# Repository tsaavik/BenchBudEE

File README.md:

BenchBudEE
==========

The Session 1 Project For Contextual Electronics  
More info here: http://contextualelectronics.com/the-benchbudee/

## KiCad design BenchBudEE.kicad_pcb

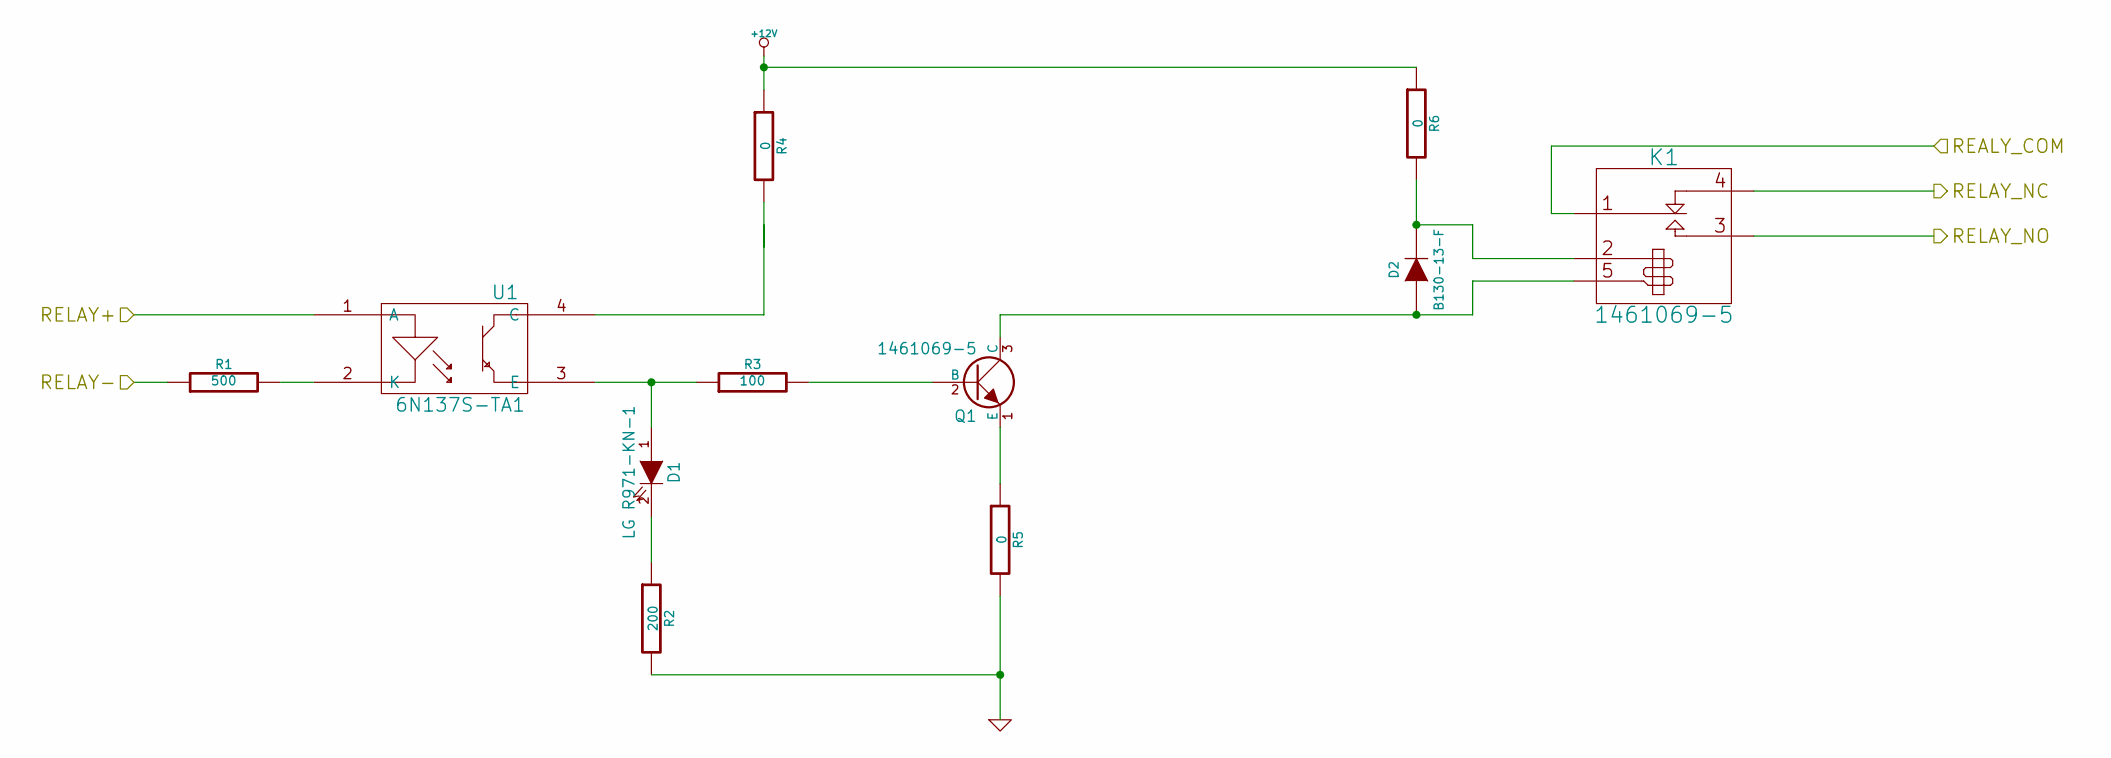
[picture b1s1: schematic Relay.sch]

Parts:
D1: LG R971-KN-1
D2: B130-13-F; MFG Part Number B130-13-F
K1: 1461069-5
Q1: 1461069-5; MFG Part Number 1461069-5
R1: 500
R2: 200
R3: 100
R4, R5, R6: 0
U1: 6N137S-TA1; MFG Part Number 6N137S-TA1

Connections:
+12V: R4.1, R6.1; also elsewhere on the board
/Relay/REALY_COM: K1.1 (C1); also elsewhere on the board
/Relay/RELAY+: U1.1 (A); also elsewhere on the board
/Relay/RELAY-: R1.1; also elsewhere on the board
/Relay/RELAY_NC: K1.4 (NC); also elsewhere on the board
/Relay/RELAY_NO: K1.3 (NO); also elsewhere on the board
GND: R2.2, R5.2; also elsewhere on the board
unnamed: R1.2, U1.2 (K)
unnamed: D2.2 (K), K1.2 (Coil+), R6.2
unnamed: D2.1 (A), K1.5 (Coil-), Q1.3 (C)
unnamed: D1.2 (K), R2.1
unnamed: R4.2, U1.4 (C)
unnamed: Q1.1 (E), R5.1
unnamed: Q1.2 (B), R3.2
unnamed: D1.1 (A), R3.1, U1.3 (E)

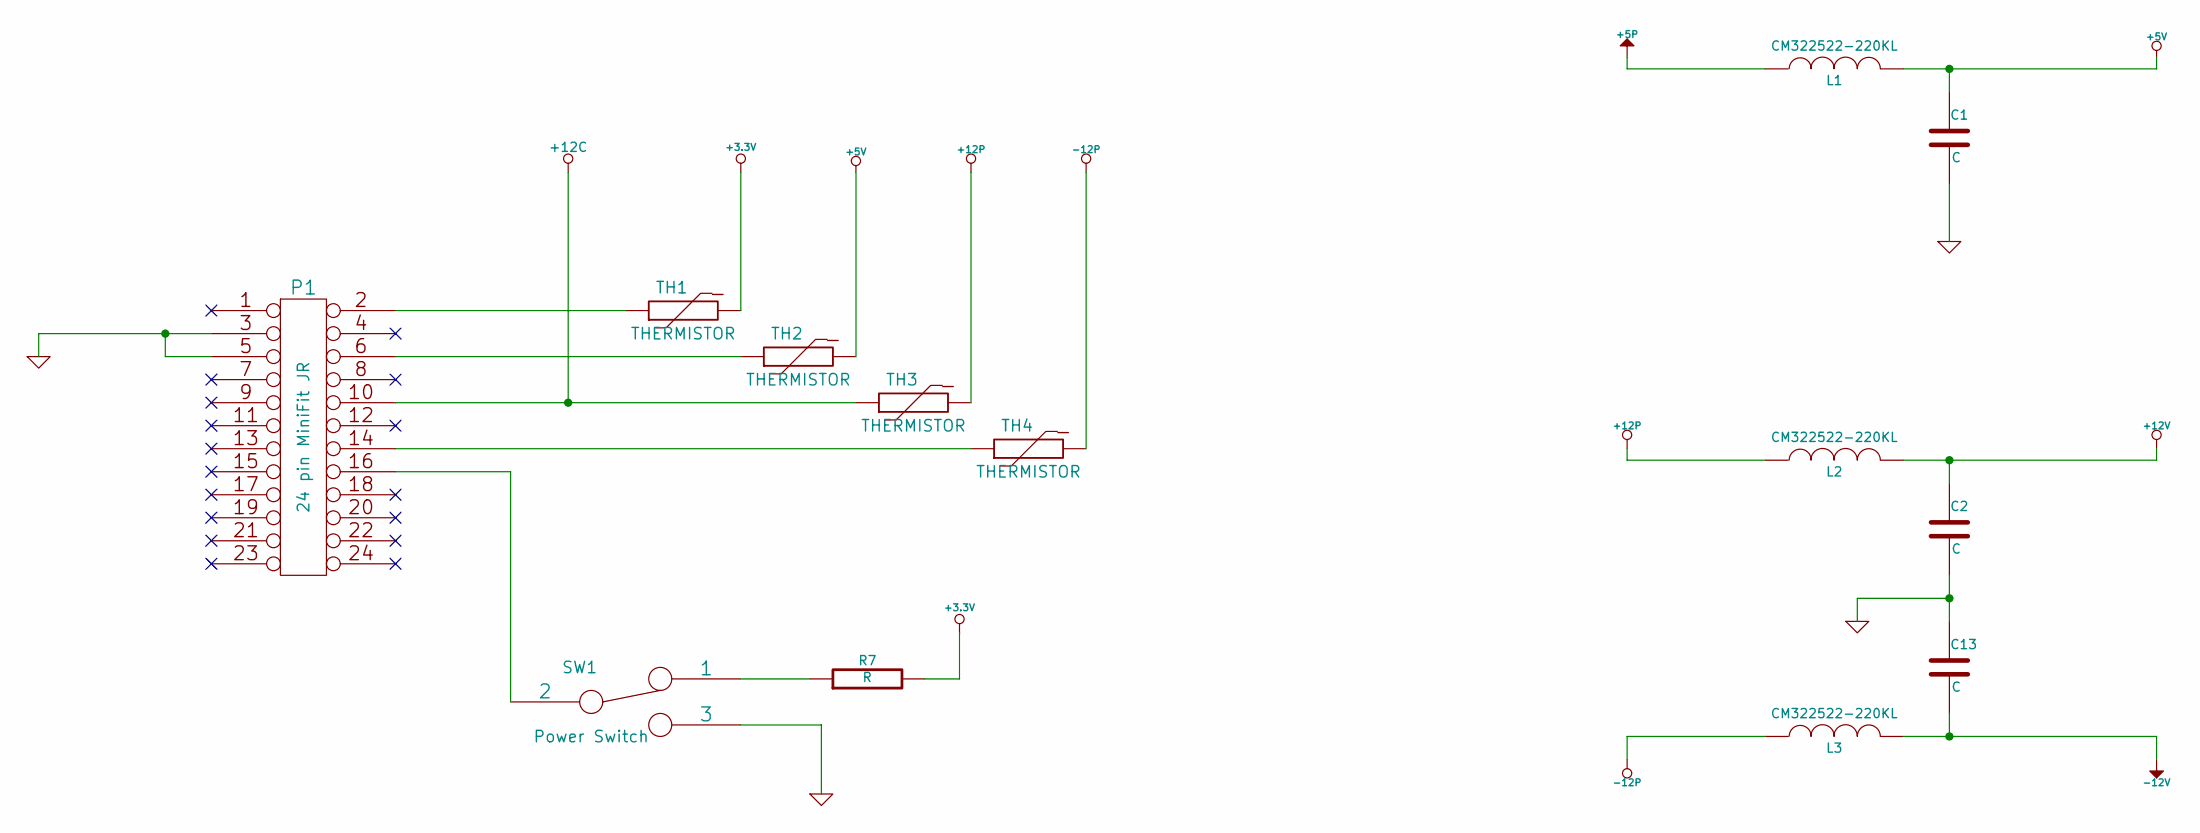
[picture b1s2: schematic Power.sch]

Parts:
C1, C2, C13: C
L1, L2, L3: CM322522-220KL; MFG Part Number CM322522-220KL
P1: 24 pin MiniFit JR; MFG Part Number 39-30-1240
R7: R
SW1: Power Switch; MFG Part Number OS102011MA1QN1
TH1, TH2, TH3, TH4: THERMISTOR; MFG Part Number MINISMDC050F-2

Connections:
+3.3V: R7.2, TH1.2; also elsewhere on the board
+5V: C1.1, L1.2, TH2.2; also elsewhere on the board
+12C: P1.10, TH3.1
+12P: L2.1, TH3.2; also elsewhere on the board
+12V: C2.1, L2.2; also elsewhere on the board
-12P: L3.1, TH4.2
-12V: C13.2, L3.2; also elsewhere on the board
GND: C1.2, C2.2, C13.1, P1.3, P1.5, SW1.3; also elsewhere on the board
unnamed: P1.14, TH4.1
unnamed: P1.6, TH2.1
unnamed: P1.2, TH1.1
unnamed: P1.16, SW1.2
unnamed: R7.1, SW1.1

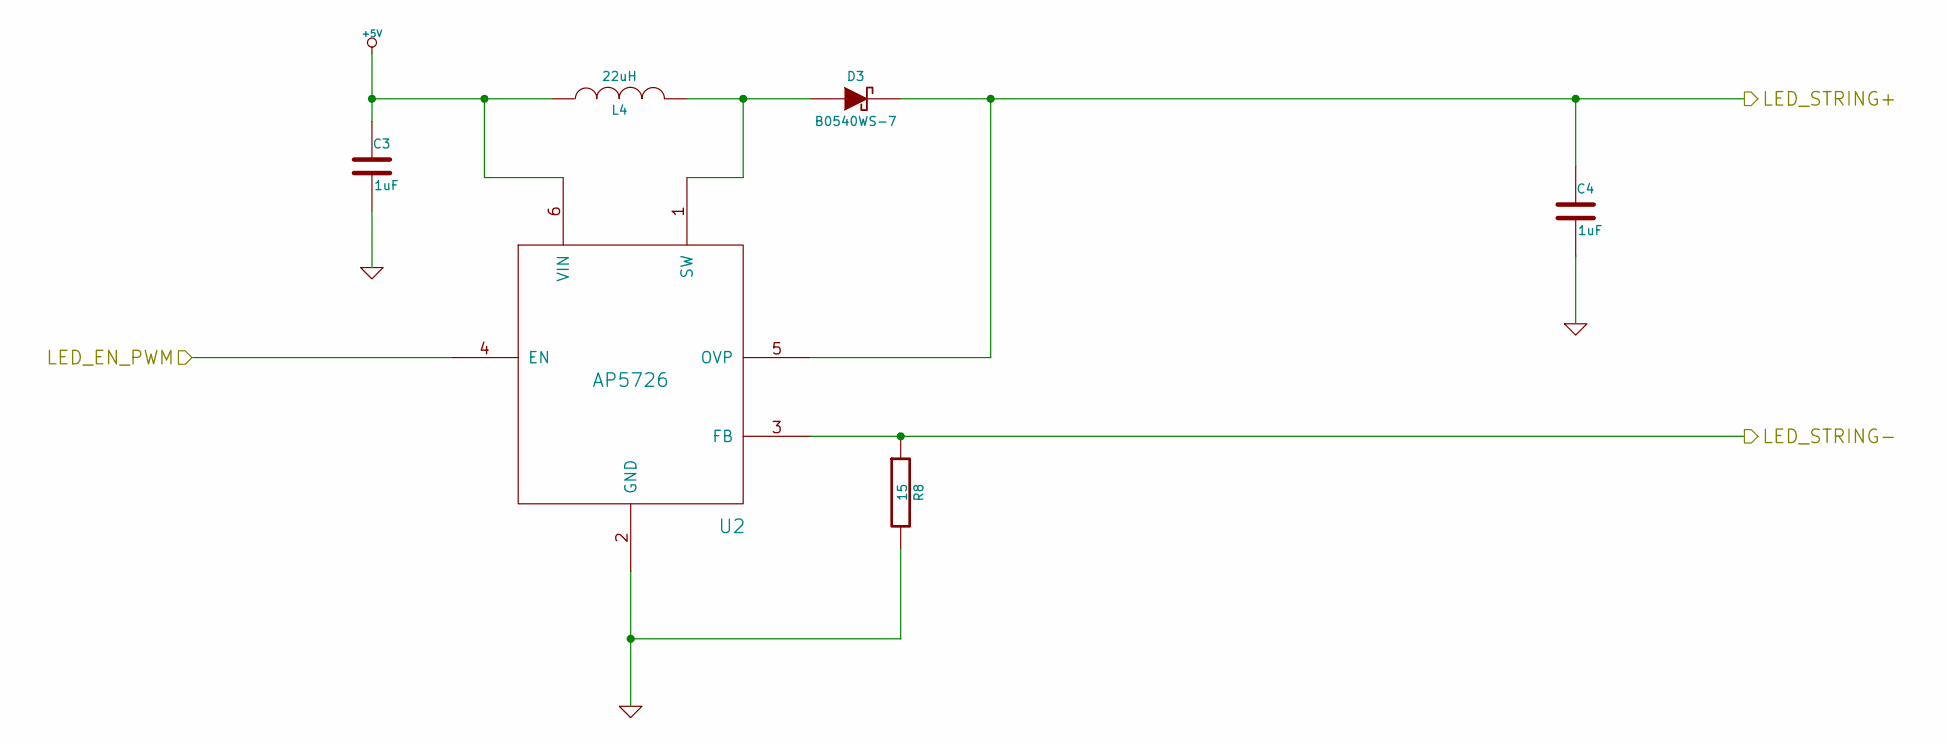
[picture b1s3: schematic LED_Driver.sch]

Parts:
C3, C4: 1uF
D3: B0540WS-7; MFG Part Number B0540WS-7
L4: 22uH; MFG Part Number NR4012T220M
R8: 15
U2: AP5726

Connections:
+5V: C3.1, L4.1, U2.6 (VIN); also elsewhere on the board
/Arduino/LED_EN_PWM: U2.4 (EN); also elsewhere on the board
/LED_Driver/LED_STRING+: C4.1, D3.2 (K), U2.5 (OVP); also elsewhere on the board
/LED_Driver/LED_STRING-: R8.1, U2.3 (FB); also elsewhere on the board
GND: C3.2, C4.2, R8.2, U2.2 (GND); also elsewhere on the board
unnamed: D3.1 (A), L4.2, U2.1 (SW)

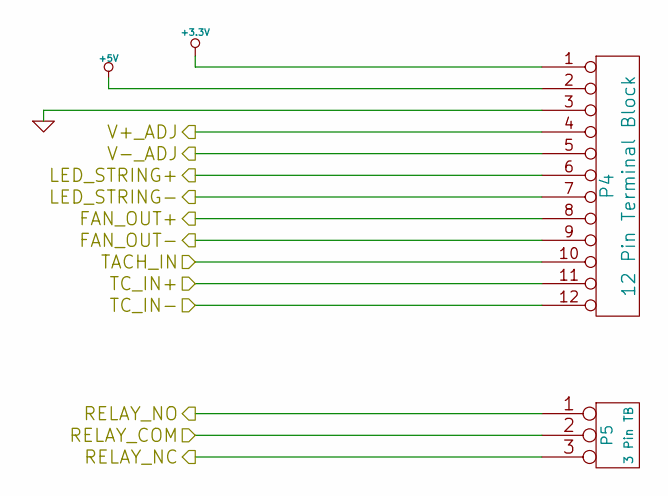
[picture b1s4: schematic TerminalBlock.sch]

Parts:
P4: 12 Pin Terminal Block; MFG Part Number 1706251
P5: 3 Pin TB; MFG Part Number 1990986

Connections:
+3.3V: P4.1; also elsewhere on the board
+5V: P4.2; also elsewhere on the board
/Fan/FAN_OUT+: P4.8; also elsewhere on the board
/Fan/FAN_OUT-: P4.9; also elsewhere on the board
/Fan/TACH_IN: P4.10; also elsewhere on the board
/LED_Driver/LED_STRING+: P4.6; also elsewhere on the board
/LED_Driver/LED_STRING-: P4.7; also elsewhere on the board
/PowerAdjustmentMonitor/V+_ADJ: P4.4; also elsewhere on the board
/PowerAdjustmentMonitor/V-_ADJ: P4.5; also elsewhere on the board
/Relay/REALY_COM: P5.2 (PM); also elsewhere on the board
/Relay/RELAY_NC: P5.3; also elsewhere on the board
/Relay/RELAY_NO: P5.1; also elsewhere on the board
/Thermocouple/TC IN +: P4.11; also elsewhere on the board
/Thermocouple/TC IN -: P4.12; also elsewhere on the board
GND: P4.3; also elsewhere on the board

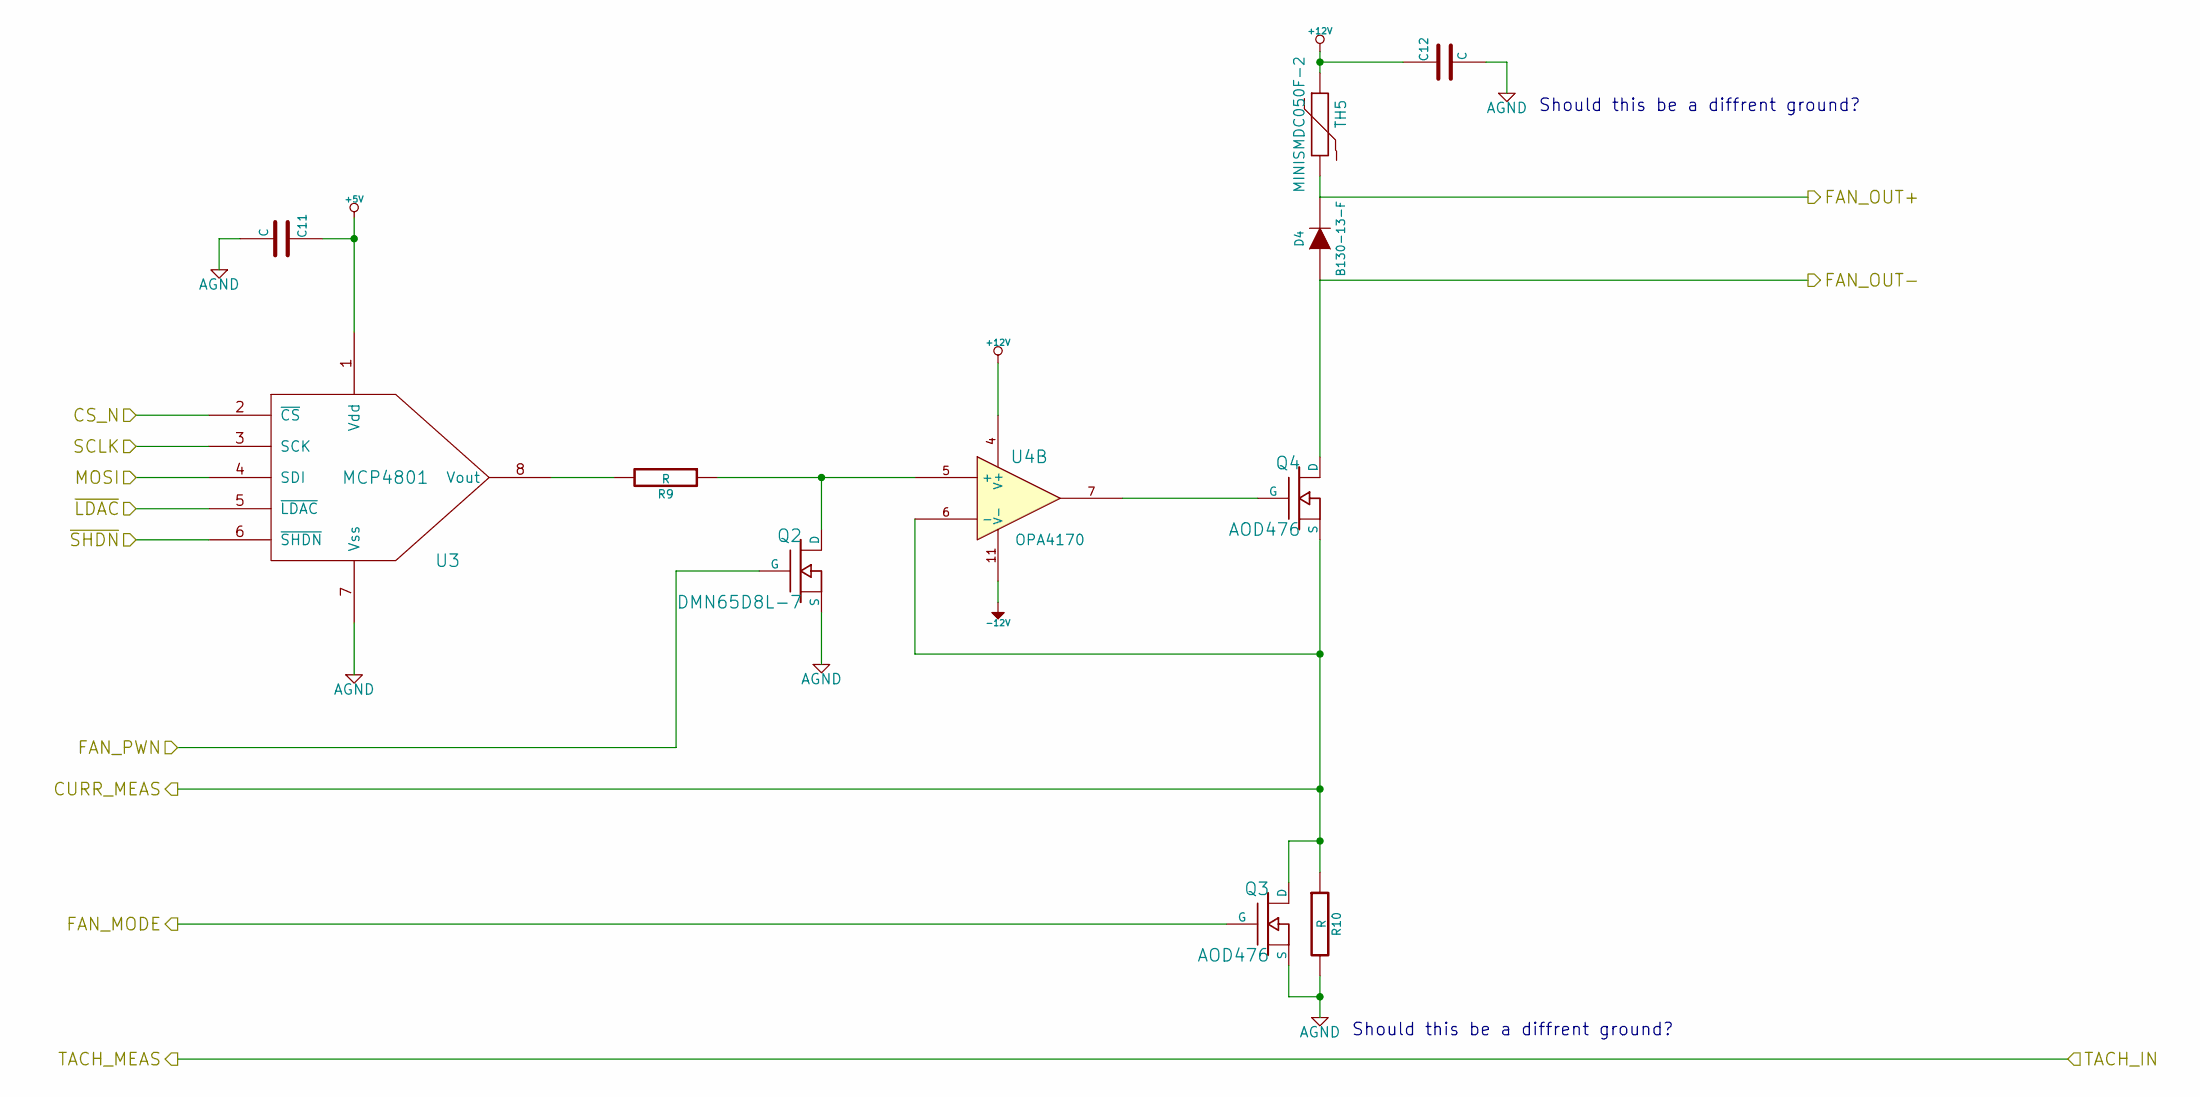
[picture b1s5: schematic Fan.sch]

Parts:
C11, C12: C
D4: B130-13-F; MFG Part Number B130-13-F
Q2: DMN65D8L-7; MFG Part Number DMN65D8L-7
Q3, Q4: AOD476; MFG Part Number AOD476
R9, R10: R
TH5: MINISMDC050F-2; MFG Part Number MINISMDC050F-2
U3: MCP4801
U4: OPA4170

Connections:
+5V: C11.1, U3.1 (Vdd); also elsewhere on the board
+12V: C12.1, TH5.1, U4.4 (V+); also elsewhere on the board
-12V: U4.11 (V-); also elsewhere on the board
/Arduino/CURR_MEAS: Q3.2 (D), Q4.3 (S), R10.1, U4.6 (-); also elsewhere on the board
/Arduino/FAN_MODE: Q3.1 (G); also elsewhere on the board
/Arduino/FAN_PWM: Q2.G; also elsewhere on the board
/Arduino/MOSI: U3.4 (SDI); also elsewhere on the board
/Arduino/SCLK: U3.3 (SCK); also elsewhere on the board
/Arduino/~LDAC: U3.5 (~LDAC); also elsewhere on the board
/Arduino/~SHDN: U3.6 (~SHDN); also elsewhere on the board
/Fan/CS_N: U3.2 (~CS); also elsewhere on the board
/Fan/FAN_OUT+: D4.2 (K), TH5.2; also elsewhere on the board
/Fan/FAN_OUT-: D4.1 (A), Q4.2 (D); also elsewhere on the board
AGND: C11.2, C12.2, Q2.S, Q3.3 (S), R10.2, U3.7 (Vss); also elsewhere on the board
unnamed: Q4.1 (G), U4.7
unnamed: Q2.D, R9.1, U4.5 (+)
unnamed: R9.2, U3.8 (Vout)

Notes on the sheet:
Should this be a diffrent ground?

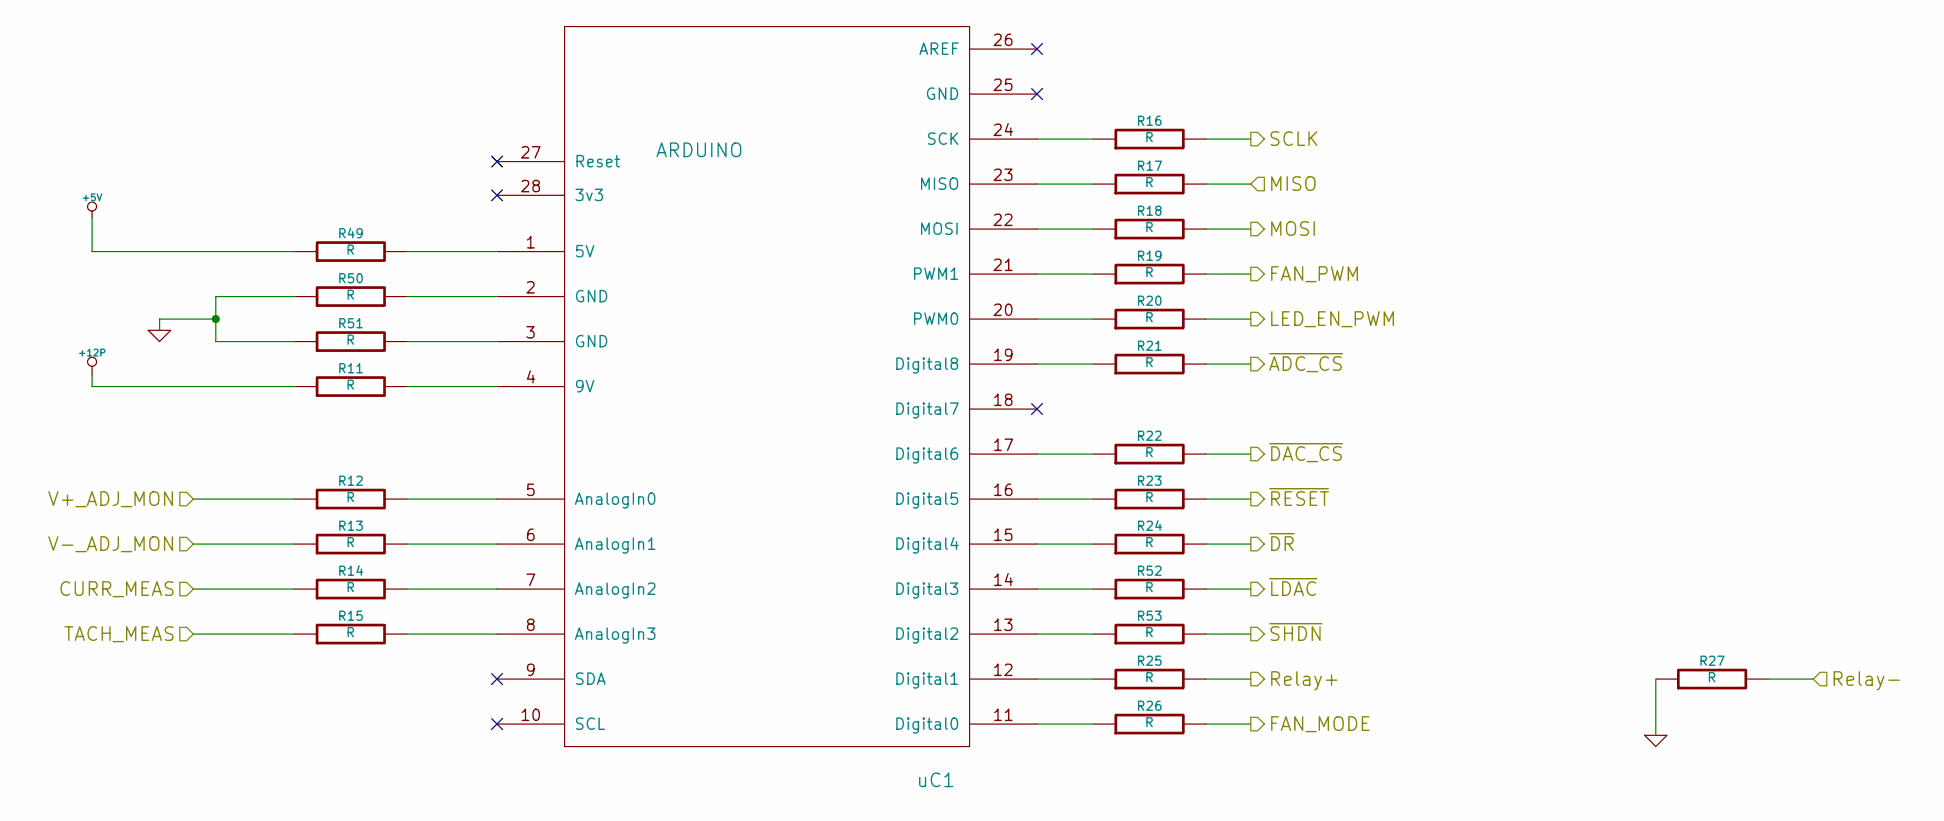
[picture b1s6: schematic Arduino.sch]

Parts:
R11, R12, R13, R14, R15, R16, R17, R18, R19, R20, R21, R22, R23, R24, R25, R26, R27, R49, R50, R51, R52, R53: R
uC1: ARDUINO

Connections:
+5V: R49.1; also elsewhere on the board
+12P: R11.1; also elsewhere on the board
/Arduino/CURR_MEAS: R14.1; also elsewhere on the board
/Arduino/FAN_MODE: R26.2; also elsewhere on the board
/Arduino/FAN_PWM: R19.2; also elsewhere on the board
/Arduino/LED_EN_PWM: R20.2; also elsewhere on the board
/Arduino/MISO: R17.2; also elsewhere on the board
/Arduino/MOSI: R18.2; also elsewhere on the board
/Arduino/SCLK: R16.2; also elsewhere on the board
/Arduino/V+_ADJ_MON: R12.1; also elsewhere on the board
/Arduino/V-_ADJ_MON: R13.1; also elsewhere on the board
/Arduino/~ADC_CS: R21.2; also elsewhere on the board
/Arduino/~DR: R24.2; also elsewhere on the board
/Arduino/~LDAC: R52.2; also elsewhere on the board
/Arduino/~RESET: R23.2; also elsewhere on the board
/Arduino/~SHDN: R53.2; also elsewhere on the board
/Fan/CS_N: R22.2; also elsewhere on the board
/Fan/TACH_IN: R15.1; also elsewhere on the board
/Relay/RELAY+: R25.2; also elsewhere on the board
/Relay/RELAY-: R27.2; also elsewhere on the board
GND: R27.1, R50.1, R51.1; also elsewhere on the board
unnamed: R25.1, uC1.12 (Digital1)
unnamed: R19.1, uC1.21 (PWM1)
unnamed: R21.1, uC1.19 (Digital8)
unnamed: R18.1, uC1.22 (MOSI)
unnamed: R16.1, uC1.24 (SCK)
unnamed: R11.2, uC1.4 (9V)
unnamed: R26.1, uC1.11 (Digital0)
unnamed: R22.1, uC1.17 (Digital6)
unnamed: R20.1, uC1.20 (PWM0)
unnamed: R15.2, uC1.8 (AnalogIn3)
unnamed: R14.2, uC1.7 (AnalogIn2)
unnamed: R13.2, uC1.6 (AnalogIn1)
unnamed: R12.2, uC1.5 (AnalogIn0)
unnamed: R17.1, uC1.23 (MISO)
unnamed: R49.2, uC1.1 (5V)
unnamed: R51.2, uC1.3 (GND)
unnamed: R50.2, uC1.2 (GND)
unnamed: R23.1, uC1.16 (Digital5)
unnamed: R53.1, uC1.13 (Digital2)
unnamed: R52.1, uC1.14 (Digital3)
unnamed: R24.1, uC1.15 (Digital4)

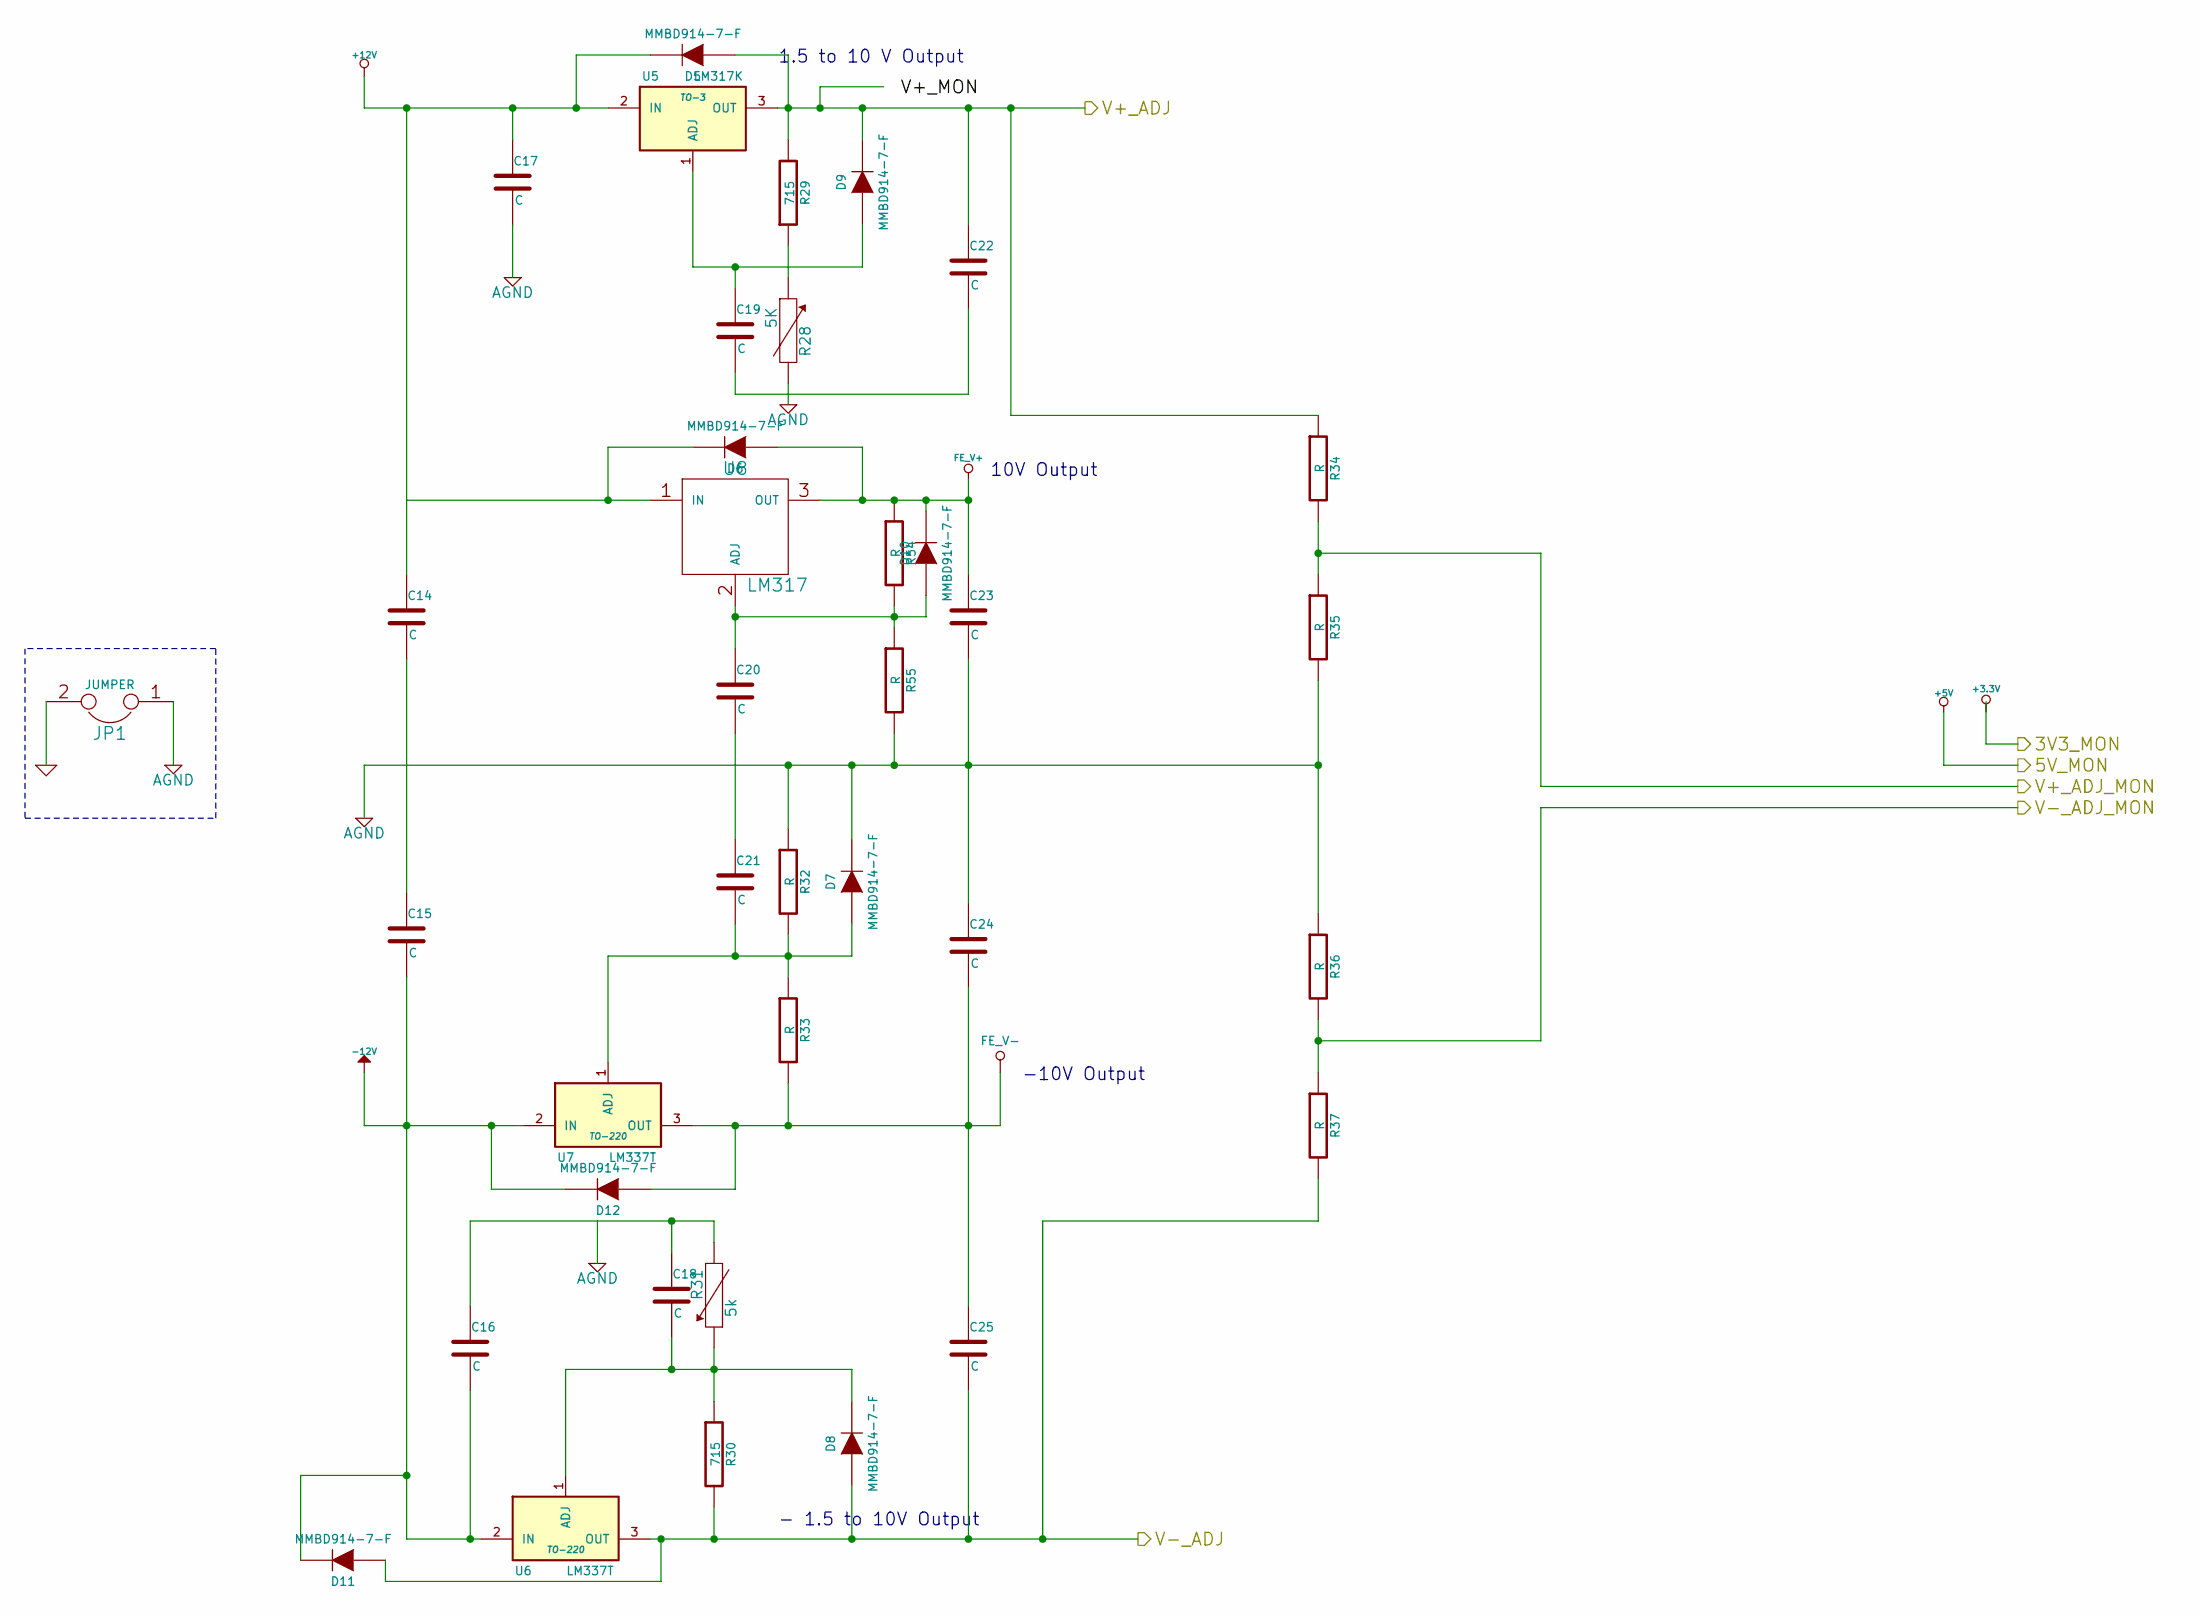
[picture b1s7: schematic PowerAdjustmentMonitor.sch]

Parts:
C14, C15, C16, C17, C18, C19, C20, C21, C22, C23, C24, C25: C
D5, D6, D7, D8, D9, D10, D11, D12: MMBD914-7-F
JP1: JUMPER
R28: 5K
R29: 715
R30: 715
R31: 5k
R32, R33, R54, R55: R
R34, R35, R36, R37: R
U5: LM317K; TO-3
U6, U7: LM337T; TO-220
U8: LM317

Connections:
+12V: C14.1, C17.1, D5.2 (K), U5.2 (IN); also elsewhere on the board
-12V: C15.2, C16.2, D11.2 (K), D12.2 (K), U6.2 (IN), U7.2 (IN); also elsewhere on the board
/Arduino/V+_ADJ_MON: R34.2, R35.1; also elsewhere on the board
/Arduino/V-_ADJ_MON: R36.2, R37.1; also elsewhere on the board
/PowerAdjustmentMonitor/V+_ADJ: C22.1, D5.1 (A), D9.2 (K), R29.2, R34.1, U5.3 (OUT); also elsewhere on the board
/PowerAdjustmentMonitor/V-_ADJ: C25.2, D8.1 (A), D11.1 (A), R30.2, R37.2, U6.3 (OUT); also elsewhere on the board
AGND: C17.2, C23.2, C24.1, D7.2 (K), JP1.1, R28.2, R32.1, R35.2, R36.1, R55.2; also elsewhere on the board
FE_V+: C23.1, D6.1 (A), D10.2 (K), R54.1, U8.3 (OUT)
FE_V-: C24.2, C25.1, D12.1 (A), R33.2, U7.3 (OUT)
GND: JP1.2; also elsewhere on the board
unnamed: C20.2, C21.1
unnamed: C16.1, C18.1, R31.2
unnamed: C19.2, C22.2
unnamed: C14.2, C15.1
unnamed: R28.1, R29.1
unnamed: C19.1, D9.1 (A), U5.1 (ADJ)
unnamed: D6.2 (K), U8.1 (IN)
unnamed: C20.1, D10.1 (A), R54.2, R55.1, U8.2 (ADJ)
unnamed: C21.2, D7.1 (A), R32.2, R33.1, U7.1 (ADJ)
unnamed: C18.2, D8.2 (K), R30.1, R31.1, U6.1 (ADJ)

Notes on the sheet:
1.5 to 10 V Output
10V Output
-10V Output
- 1.5 to 10V Output

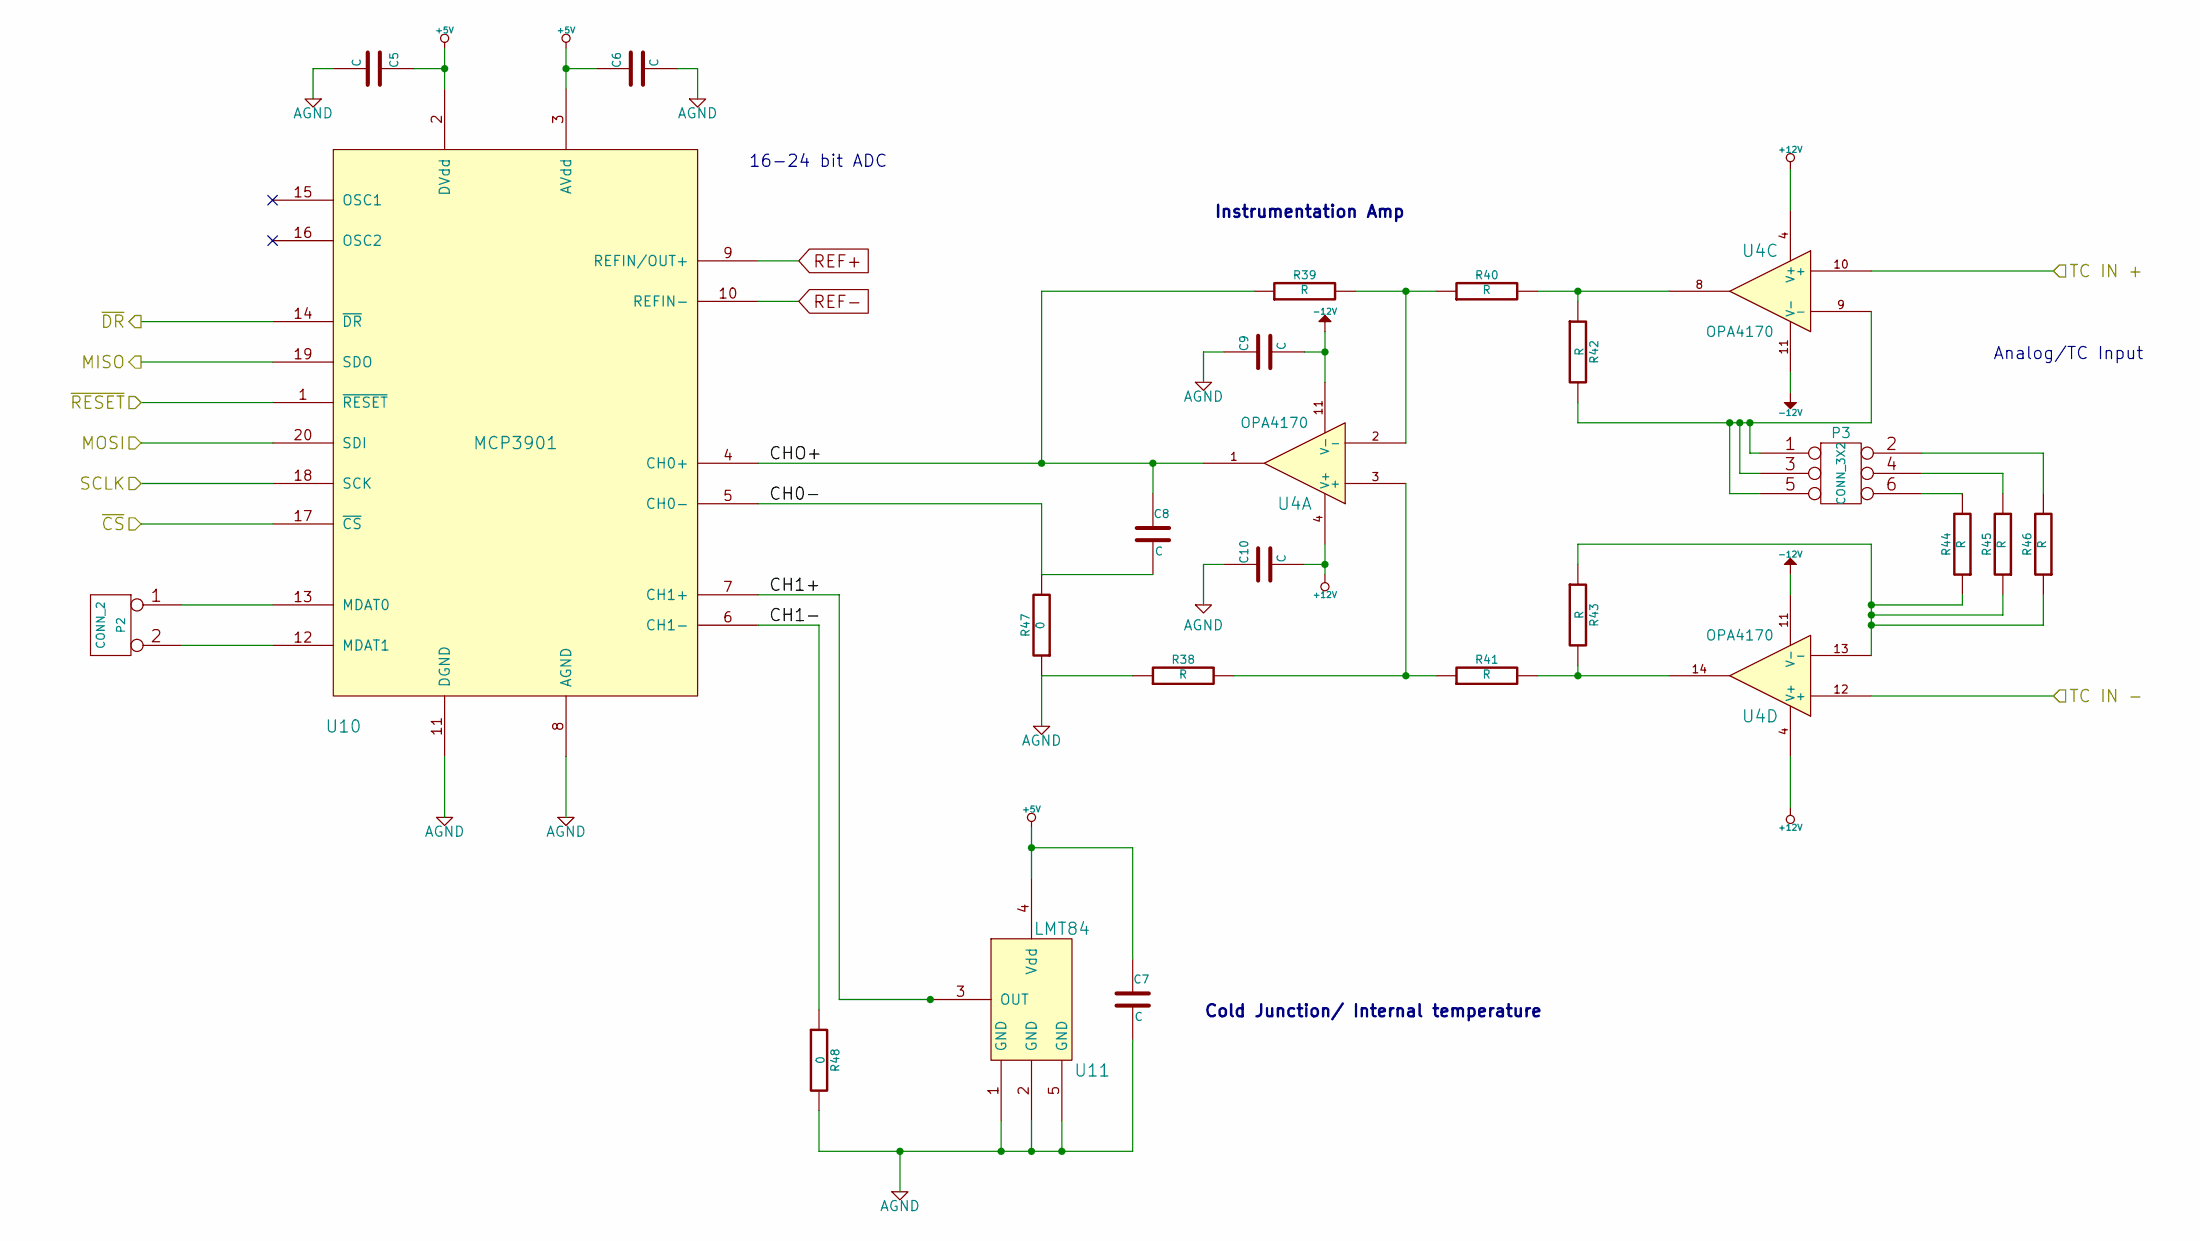
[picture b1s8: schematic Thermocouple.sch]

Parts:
C5, C6, C7, C8, C9, C10: C
P2: CONN_2
P3: CONN_3X2
R38, R39, R40, R41, R42, R43, R44, R45, R46: R
R47, R48: 0
U4: OPA4170
U10: MCP3901
U11: LMT84

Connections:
+5V: C5.1, C6.1, C7.1, U10.2 (DVdd), U10.3 (AVdd), U11.4 (Vdd); also elsewhere on the board
+12V: C10.2, U4.4 (V+); also elsewhere on the board
-12V: C9.2, U4.11 (V-); also elsewhere on the board
/Arduino/MISO: U10.19 (SDO); also elsewhere on the board
/Arduino/MOSI: U10.20 (SDI); also elsewhere on the board
/Arduino/SCLK: U10.18 (SCK); also elsewhere on the board
/Arduino/~ADC_CS: U10.17 (~CS); also elsewhere on the board
/Arduino/~DR: U10.14 (~DR); also elsewhere on the board
/Arduino/~RESET: U10.1 (~RESET); also elsewhere on the board
/Thermocouple/CH0-: C8.2, R47.2, U10.5 (CH0-)
/Thermocouple/CH1+: U10.7 (CH1+), U11.3 (OUT)
/Thermocouple/CH1-: R48.1, U10.6 (CH1-)
/Thermocouple/CHO+: C8.1, R39.1, U4.1, U10.4 (CH0+)
/Thermocouple/TC IN +: U4.10 (+); also elsewhere on the board
/Thermocouple/TC IN -: U4.12 (+); also elsewhere on the board
AGND: C5.2, C6.2, C7.2, C9.1, C10.1, R38.1, R47.1, R48.2, U10.8 (AGND), U10.11 (DGND), U11.1 (GND), U11.2 (GND), U11.5 (GND); also elsewhere on the board
unnamed: P2.1, U10.13 (MDAT0)
unnamed: P2.2 (PM), U10.12 (MDAT1)
unnamed: P3.2, R46.2
unnamed: P3.4, R45.2
unnamed: P3.6, R44.2
unnamed: R41.2, R43.2, U4.14
unnamed: R40.2, R42.1, U4.8
unnamed: R39.2, R40.1, U4.2 (-)
unnamed: R38.2, R41.1, U4.3 (+)
unnamed: R43.1, R44.1, R45.1, R46.1, U4.13 (-)
unnamed: P3.1, P3.3, P3.5, R42.2, U4.9 (-)

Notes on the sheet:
Instrumentation Amp
Cold Junction/ Internal temperature
16-24 bit ADC
Analog/TC Input

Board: 4 copper layers, 126 parts (64 on the bottom side), 103 nets, no tracks yet.

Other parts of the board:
V2006B Heatsink, V2006B Heatsink#2: VAL**; V2006B_Heatsink

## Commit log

2014-01-30 Module 2.11: create blank schematic/layout
2014-01-31 Module 2: creating a schematic skeleton Added sub-schematics for fan/led/relay/power/etc
2014-01-31 Module 2, Unit 13 Defining Your Inputs and Outputs
2014-02-05 3.3 Thermocouple Module - Initial Design
2014-02-05 3.4 Understanding The Current/Fan Driver Module Added circuit to the Current/Fan Driver module
2014-02-07 3.5 Understanding The Relay Module
2014-02-07 3.6 Understanding The Power Protection And Filtering Module Added the power monitor/filtering sub-schematic
2014-02-07 Put the power schematic in the wrong sub-module (PowerAdjustmentMonitor)
2014-02-07 Not sure what I changed
2014-02-07 files got touched because I did a commit -a and dropbox synced it
2014-02-07 3.7 Understanding The Power Control, Conditioning And Monitoring Module Prior to addition of adjustable resistor. Acidently did save-whole-project
2014-02-07 Added variable resistor(s) to LM317's output
2014-02-07 Forgot the V+_ADJ pin, fixed
2014-02-07 fixed pin name typo 5V5_MON => 5V_MON
2014-02-07 Added hierarchical pins to PowerAdjustmentMonitor
2014-02-08 Added AP5726 led dimmer chip to local library
2014-02-08 3.8 Understanding The LED Driver Module
2014-02-10 3.9 Added Arduino
2014-02-10 3.9 Understanding The Arduino Module Added content to Arduino and block (header) modules
2014-02-10 3.10 Revisiting The Current/Fan Module End of Module 3, lots of cleanup/changes all over the place.
2014-02-13 Fixed a mistake on the arduino Digital pins
2014-02-13 replaced faulty arduino part with updated library
2014-02-16 added *bak to prevent checkin of board backups
2014-02-16 4.18 Initial board layout and design rules mods
2014-02-16 Keyboard shortcuts for BenchBudEE (changed layer selection keys 1-9)
2014-02-16 4.18 Video 2 Changed design rules for pin spacing
2014-02-18 Update README.md
    added image
2014-02-19 5.3 Video 1/2 Associating and Placing the Relay Module
2014-02-20 Added te-spdt relay, sma and smd-8 footprints
2014-02-20 5.3 Video 2/2 Associating and Placing the Relay Module
2014-02-21 5.4 Video 1/2 Associating and Placing the Thermocouple Module
2014-02-21 added another kicad backup type
2014-02-22 5.4 Video 2/2 Associating and Placing the Thermocouple Module
2014-02-22 Unknown changes
2014-02-22 5.6 Video 1/2 Associating and Placing the Terminal/ATX Blocks
2014-02-22 5.6 Video 2/2 Associating and Placing the Terminal/ATX Blocks
    Created the 12pin, 3 pin and atx connector footprints and placed
2014-02-22 5.6 Associating and Placing the Arduino Module
    Added Arduino and 0805_blob footprints, placed arduino board
2014-02-23 5.7 Video 1/2 Associating and Placing the Arduino Module
2014-02-23 5.7 Video 2/2 Associating and Placing the Arduino Module
2014-02-23 5.8 Associating and Placing the Power Protection and Filtering Module
2014-02-23 5.10 Video 1/2 Associating and Placing the Power Modification Module
2014-02-24 5.10 Video 2/2 Associating and Placing the Power Modification Module
2014-02-24 5.11 Video 1/2 Associating and Placing the LED Driver Module
2014-02-24 5.11 Video 2/2 Associating and Placing the LED Driver Module
2014-02-24 5.13 Video 1/2 @ 12m:30s Finalizing The System Part Placement
2014-02-24 5.13 Video 1/2 Finalizing The System Part Placement
2014-02-24 5.13 Video 2/2 Finalizing The System Part Placement
2014-02-24 Cleanup/ERC checks, etc (on my own, no video)
2014-06-03 Relay test program, ironicly untested as of Jun 3rd 2014
2014-06-03 whitespace and comments
2014-06-03 Initial checking of DAC test program, untested as of Jun 3rd 2014
2014-06-03 Added Arduino function calls for LSB/MSB that Wizzy published
2014-06-03 Changed ints to constants
2014-06-04 Added additonal comments about ldac
